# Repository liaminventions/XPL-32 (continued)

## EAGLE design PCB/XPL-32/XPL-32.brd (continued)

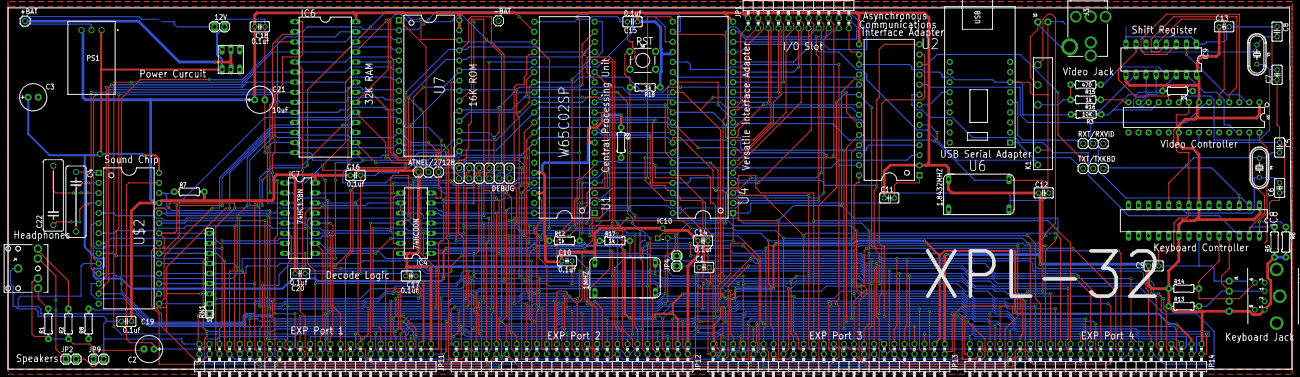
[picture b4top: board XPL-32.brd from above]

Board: 2 copper layers, 323.8 x 91.1 mm, 81 parts (1 on the bottom side), 116 nets.

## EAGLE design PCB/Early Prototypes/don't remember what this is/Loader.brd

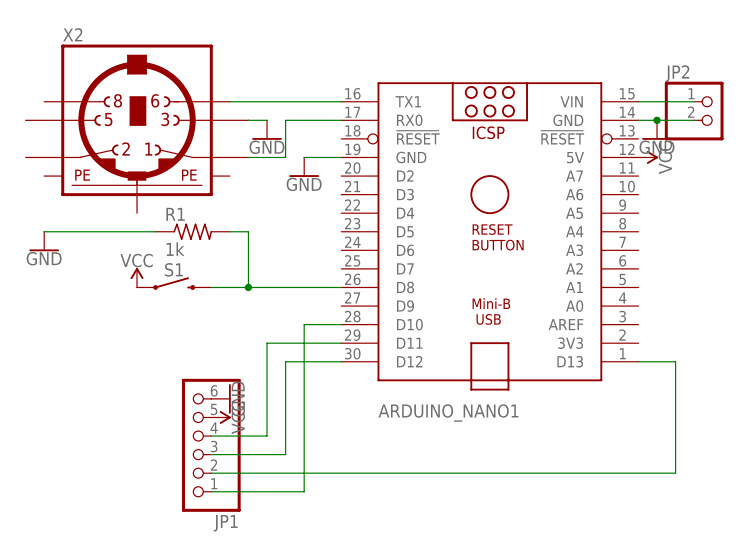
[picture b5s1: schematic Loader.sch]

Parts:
ARDUINO_NANO1: ARDUINO_NANO
JP1: PINHD-1X6; 1X06
JP2: PINHD-1X2; 1X02
R1: 1k; 0204/7
S1: MOMENTARY-SWITCH-SPST-PTH-6.0MM; TACTILE_SWITCH_PTH_6.0MM
X2: MINI_DIN_6; M_DIN6

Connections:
GND: ARDUINO_NANO1.14 (GND), ARDUINO_NANO1.19 (GND), JP1.6, JP2.2, R1.1, X2.3
unnamed: ARDUINO_NANO1.16 (TX1), X2.6
unnamed: ARDUINO_NANO1.17 (RX0), X2.1
unnamed: ARDUINO_NANO1.15 (VIN), JP2.1
unnamed: ARDUINO_NANO1.29 (D11), JP1.4
unnamed: ARDUINO_NANO1.30 (D12), JP1.3
unnamed: ARDUINO_NANO1.1 (D13), JP1.2
unnamed: ARDUINO_NANO1.28 (D10), JP1.1
unnamed: ARDUINO_NANO1.26 (D8), R1.2, S1.3 (2)
PE1: X2.SH1 (PE1)
PE2: X2.SH2 (PE2)
PE3: X2.SH3 (PE3)
VCC: ARDUINO_NANO1.12 (5V), JP1.5, S1.1

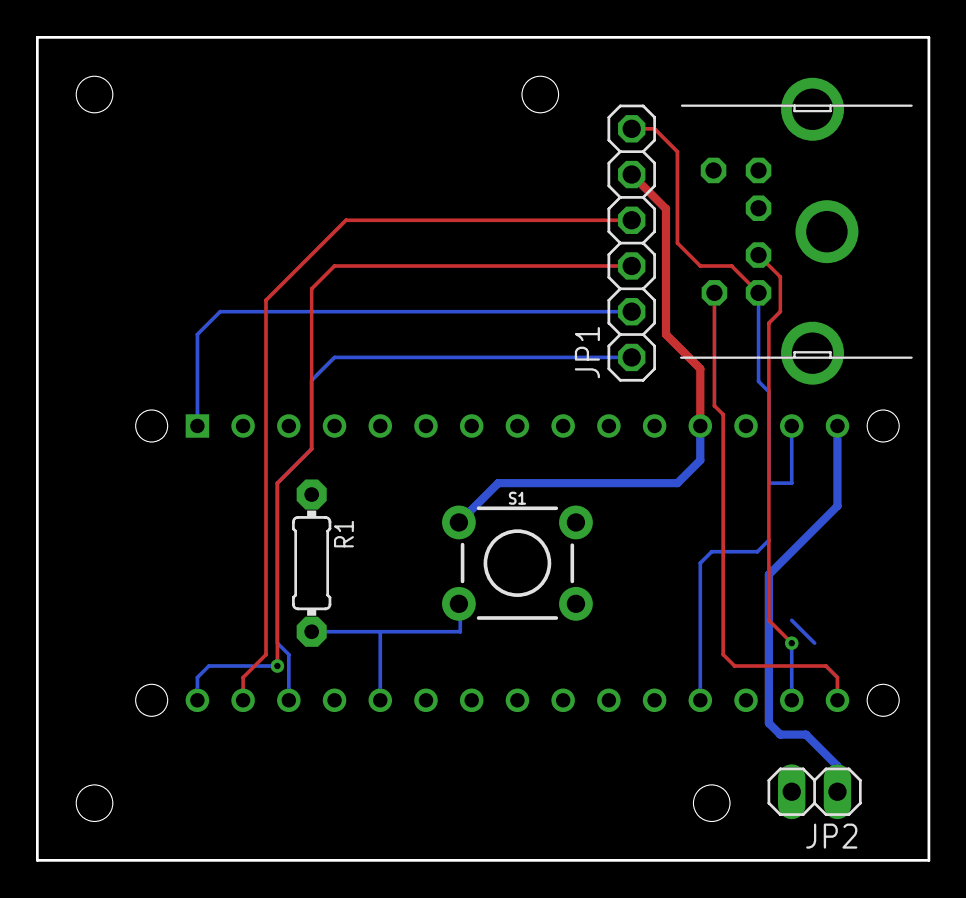
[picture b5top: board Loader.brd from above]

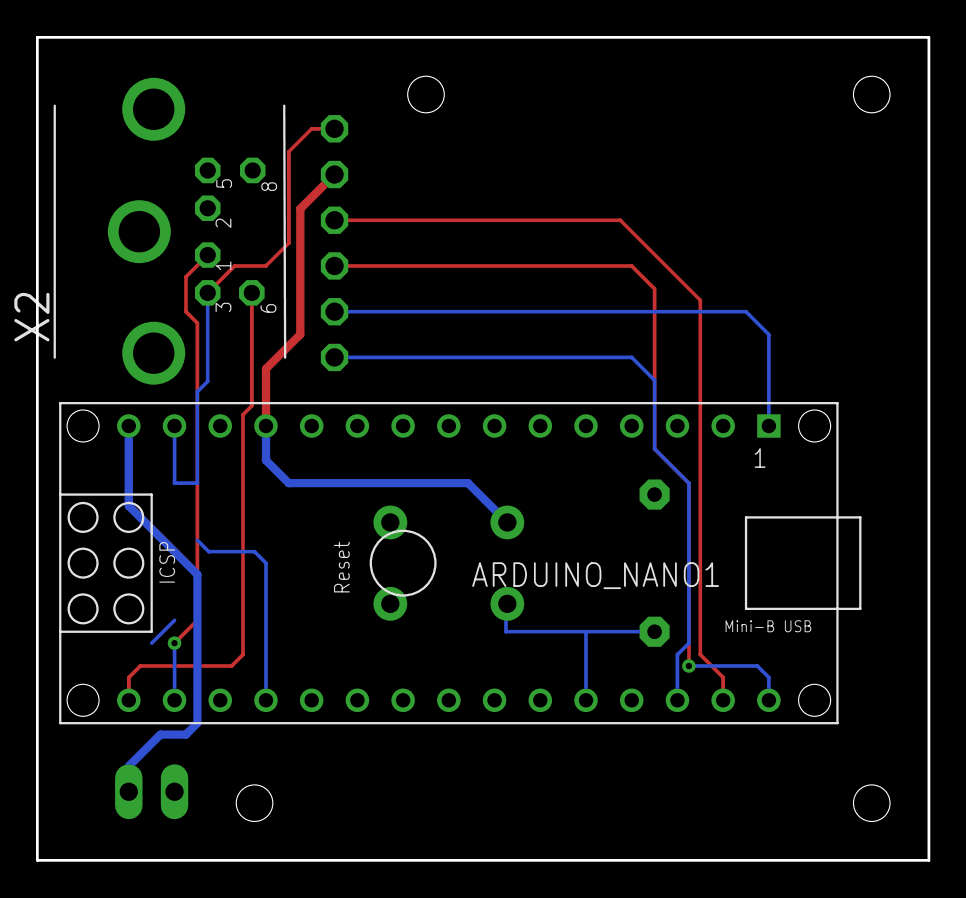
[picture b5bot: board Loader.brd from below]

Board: 2 copper layers, 49.5 x 45.7 mm, 6 parts (2 on the bottom side), 10 nets.

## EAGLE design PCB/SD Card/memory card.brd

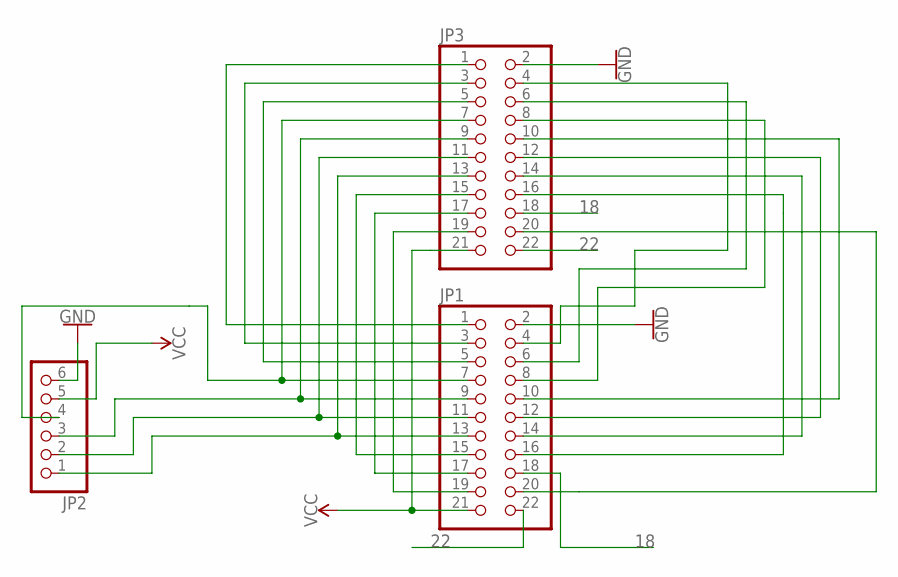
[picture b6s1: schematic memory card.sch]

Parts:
JP1, JP3: PINHD-2X11/90; 2X11/90
JP2: PINHD-1X6; 1X06

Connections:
18: JP1.18, JP3.18
22: JP1.22, JP3.22
GND: JP1.2, JP2.6, JP3.2
unnamed: JP1.20, JP3.20
unnamed: JP1.16, JP3.16
unnamed: JP1.14, JP3.14
unnamed: JP1.8, JP3.8
unnamed: JP1.19, JP3.19
unnamed: JP1.17, JP3.17
unnamed: JP1.15, JP3.15
unnamed: JP1.13, JP2.1, JP3.13
unnamed: JP1.11, JP2.2, JP3.11
unnamed: JP1.9, JP2.3, JP3.9
unnamed: JP1.7, JP2.4, JP3.7
unnamed: JP1.5, JP3.5
unnamed: JP1.3, JP3.3
unnamed: JP1.1, JP3.1
unnamed: JP1.6, JP3.6
unnamed: JP1.4, JP3.4
unnamed: JP1.12, JP3.12
unnamed: JP1.10, JP3.10
VCC: JP1.21, JP2.5, JP3.21

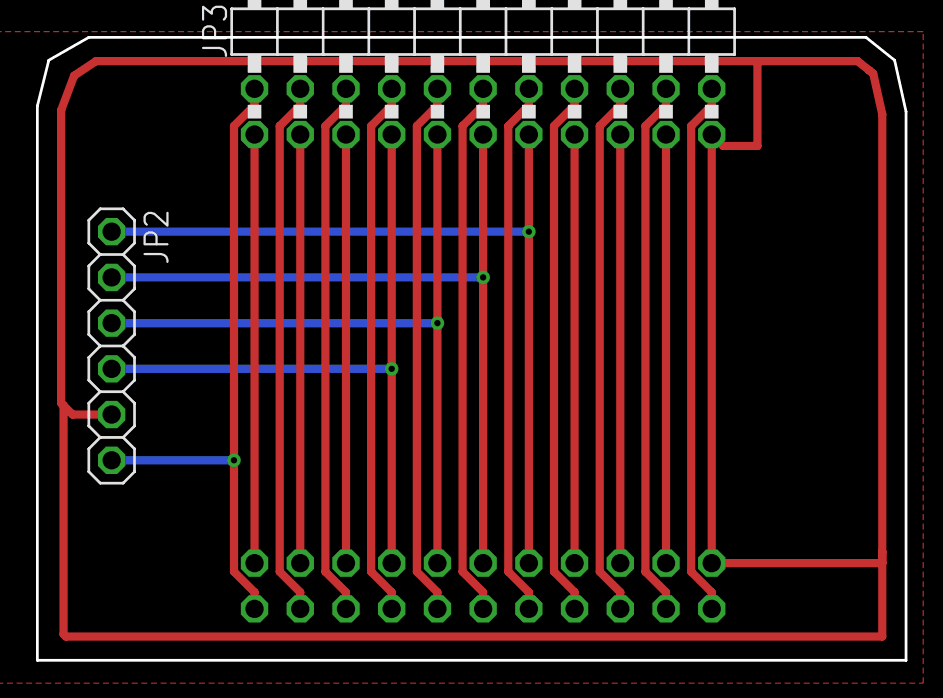
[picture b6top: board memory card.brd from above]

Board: 2 copper layers, 48.3 x 34.6 mm, 3 parts (1 on the bottom side), 22 nets.

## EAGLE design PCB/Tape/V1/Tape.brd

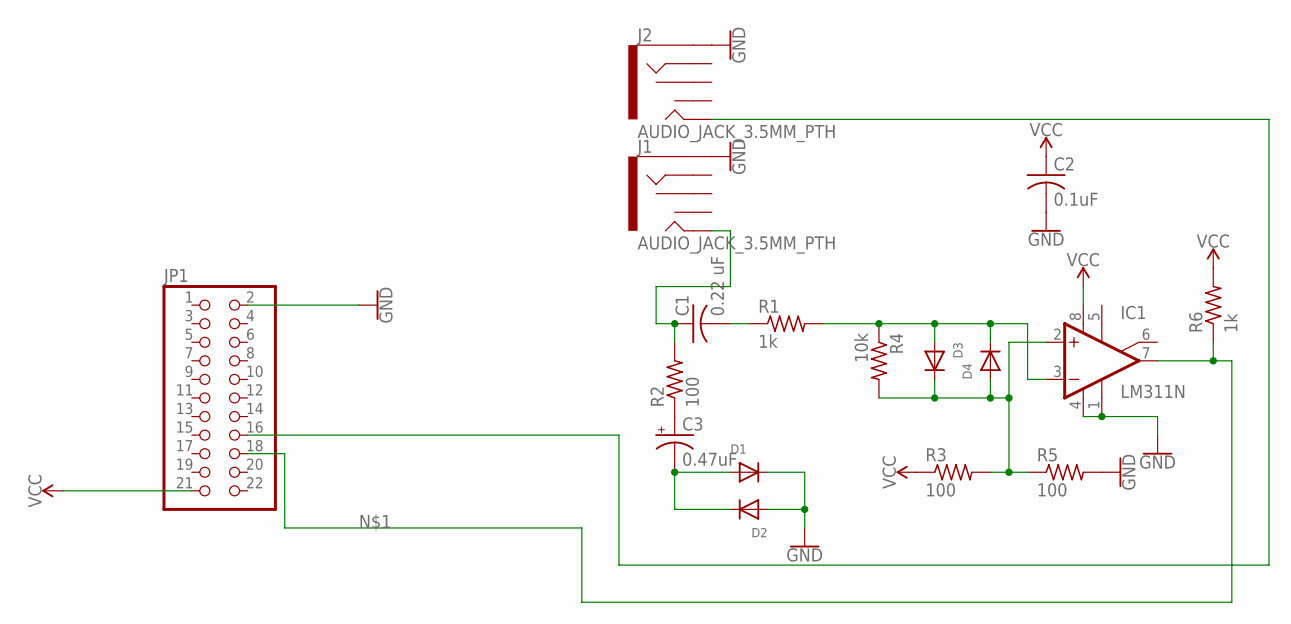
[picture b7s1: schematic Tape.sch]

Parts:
C1: 0.22 uF; C025-030X050
C2: 0.1uF; C025-030X050
C3: 0.47uF; E2,5-5
D1, D2, D3, D4: DIODEDO-1N4148; DO-1N4148
IC1: LM311N; DIL08
J1, J2: AUDIO_JACK_3.5MM_PTH; AUDIO-JACK
JP1: PINHD-2X11/90; 2X11/90
R1, R6: 1k; 0204/7
R2, R3, R5: 100; 0204/7
R4: 10k; 0204/7

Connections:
18: J2.TIP, JP1.16
GND: C2.2, D1.C, D2.A, IC1.1 (GND), IC1.4 (V-), J1.SLEEVE, J2.SLEEVE, JP1.2, R5.2
unnamed: IC1.7 (OUT), JP1.18, R6.1
unnamed: C1.2, R1.1
unnamed: C3.-, D1.A, D2.C
unnamed: C3.+, R2.1
unnamed: D3.A, D4.C, IC1.3 (-IN), R1.2, R4.1
unnamed: D3.C, D4.A, IC1.2 (+IN), R3.2, R4.2, R5.1
unnamed: C1.1, J1.TIP, R2.2
VCC: C2.1, IC1.8 (V+), JP1.21, R3.1, R6.2

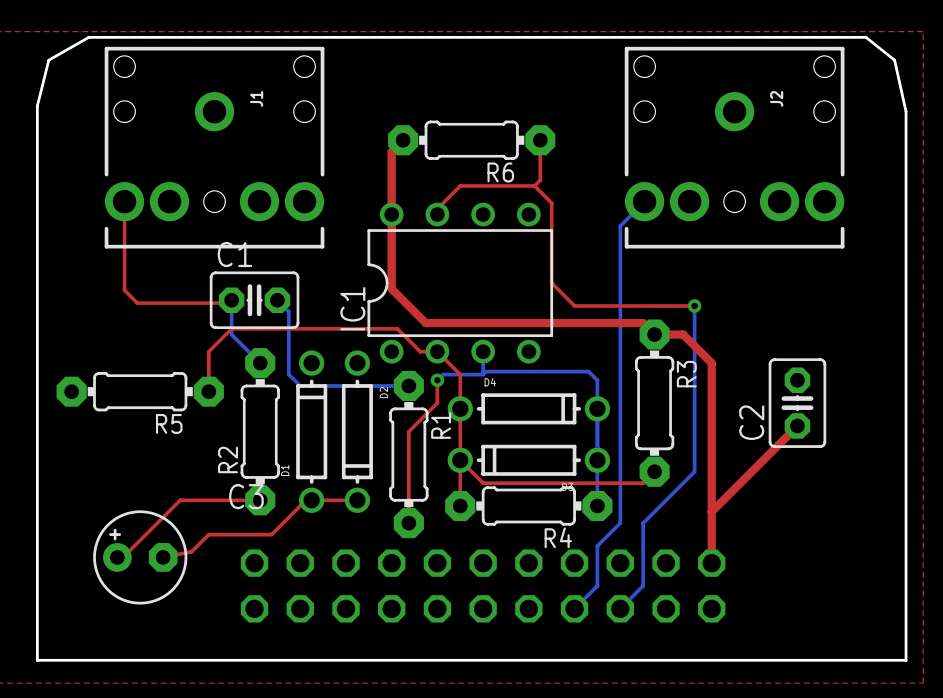
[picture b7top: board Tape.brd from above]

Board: 2 copper layers, 48.3 x 34.6 mm, 17 parts (1 on the bottom side), 10 nets.

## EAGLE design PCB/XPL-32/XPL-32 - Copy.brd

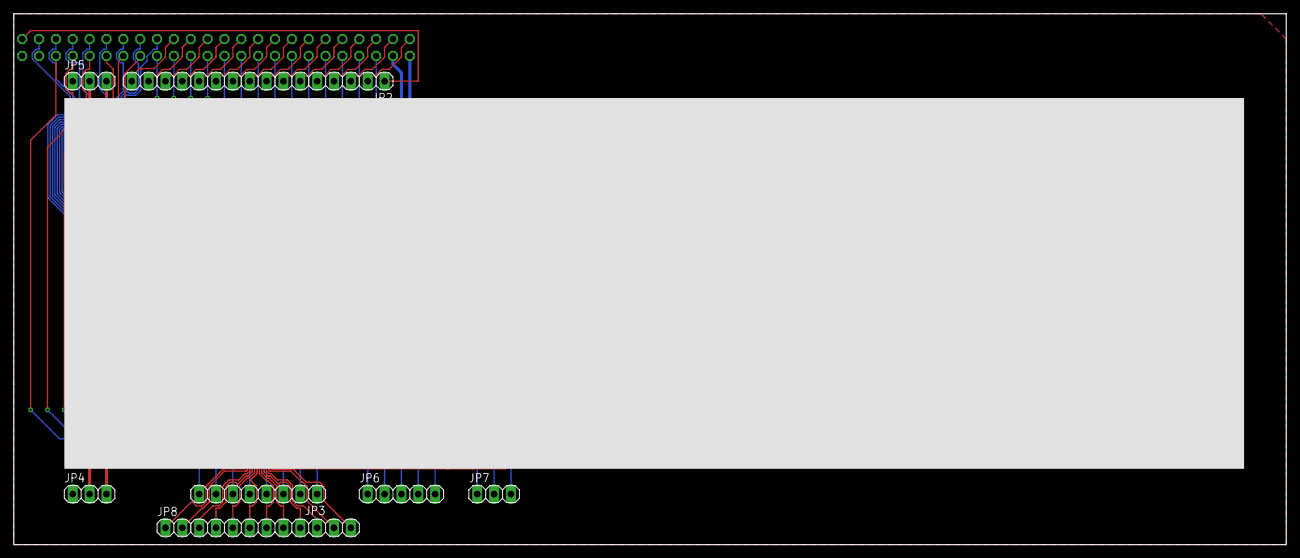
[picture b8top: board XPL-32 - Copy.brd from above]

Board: 2 copper layers, 191.8 x 80.0 mm, 8 parts (1 on the bottom side), 47 nets.

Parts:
JP1: 2X24/90
JP2: 1X16
JP3: 1X08
JP4, JP5, JP7: 1X03
JP6: 1X05
JP8: 1X12

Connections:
!8800-8FFF: JP1.15, JP6.5
!9000-97FF: JP1.17, JP6.4
!9800-9FFF: JP1.19, JP6.3
!A000-A7FF: JP1.21, JP6.2
!A800-AFFF: JP1.23, JP6.1
!CSROM: JP1.7, JP8.11
!IRQ: JP1.25, JP8.7
!OEROM: JP1.5, JP8.12
!READ: JP1.11, JP8.9
!ROM: JP1.9, JP8.10
!RST: JP1.39, JP7.3
!WRITE: JP1.13, JP8.8
A0: JP1.48, JP2.1
A1: JP1.2, JP2.2
A2: JP1.4, JP2.3
A3: JP1.6, JP2.4
A4: JP1.8, JP2.5
A5: JP1.10, JP2.6
A6: JP1.12, JP2.7
A7: JP1.14, JP2.8
A8: JP1.16, JP2.9
A9: JP1.18, JP2.10
A10: JP1.20, JP2.11
A11: JP1.22, JP2.12
A12: JP1.24, JP2.13
A13: JP1.26, JP2.14
A14: JP1.28, JP2.15
A15: JP1.30, JP2.16
AUDIO: JP1.31, JP8.4
CLK: JP1.43, JP7.1
D0: JP1.32, JP3.1
D1: JP1.34, JP3.2
D2: JP1.36, JP3.3
D3: JP1.38, JP3.4
D4: JP1.40, JP3.5
D5: JP1.42, JP3.6
D6: JP1.44, JP3.7
D7: JP1.46, JP3.8
EXTSND: JP1.33, JP8.3
EXTVID: JP1.35, JP8.2
GND: JP1.45, JP1.47, JP4.1, JP5.1
POTX: JP1.29, JP8.5
POTY: JP1.27, JP8.6
R/!W: JP1.41, JP7.2
SCLK: JP1.37, JP8.1
VCC: JP1.1, JP4.2, JP5.2
VCC_2: JP1.3, JP4.3, JP5.3

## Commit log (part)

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2023-01-01 have i fixed shortconvert?
2023-01-01 refactor
2023-01-01 maybe its not this?
2023-01-01 oqwe
2023-01-01 With this debug info, i see the issue
2023-01-01 Complete Refactor of the shortconvert system.
2023-01-01 You will work now.
2023-01-01 oh there it is! hehe
2023-01-01 all done!
2023-01-12 clean
2023-01-12 erjieqw
2023-01-12 i dont have time for this
2023-01-20 organise
2023-01-21 add clear command
2023-01-21 fix typos
2023-01-21 add slashpaths?
2023-01-21 fix addr
2023-01-21 wase of time AUUGH
2023-01-23 kernal
2023-01-24 add goofy ahh vim thingy
    aUUUGHHHHH
2023-01-24 update vi
2023-01-24 eqhruewh
2023-01-24 assemble
2023-01-24 iuir
2023-01-24 bugfix
2023-01-24 asmbler da
2023-01-24 Yes.
2023-01-27 update kernal + rearrange + fix memory overlap
2023-01-27 assemble it all together
2023-01-27 update ROM
2023-01-27 werwe
2023-01-31 ok! lets see what arrow keys are
2023-01-31 ccursor test
2023-01-31 generic commit - pay no mind
2023-02-05 add fast mode?
2023-02-05 sizing fix
2023-02-05 quik fixx
2023-02-05 add artifacts
2023-02-05 size
2023-02-05 fix tape kernal defs
2023-02-09 swap
2023-02-21 do not assemble savetest rn
    full re-write of saving
2023-02-21 he he he haw...
    this fixes lots of things...
2023-02-21 noice!
    do not use fat32 in vasm6502 yet
2023-02-21 oh yeah. this is great!
    lots of improvement, but its untested for now
2023-02-21 fix..?
2023-02-22 LETS GO !!
    i think it's done!!!!!!!
    now to test
2023-02-22 test prep (soon)
2023-02-22 testing now
2023-02-22 fix?
2023-02-22 hoho, i got u
2023-02-22 never gonna give you up
2023-02-22 Be fixed now.
2023-02-22 You are done.
2023-02-22 Fired.
2023-02-22 auugh
2023-02-22 gonna try again tomorrow
2023-02-22 oh
    dtrsynhrth
2023-02-22 ho ho ho!
    it works, but its only half a block
2023-02-22 perfect. sd_writesector works
2023-02-22 debuggin time
2023-02-23 many things :100:
    fixin gliches/debug and fix dumb mistakez (lol)
2023-02-23 remove bloat :alien:
2023-02-23 re-arrange and fix savetest i think
2023-02-23 Looking good...
    can't test it now because I didn't bring the XPL with me (on a trip)
2023-02-23 add issue
    overlooked...
2023-02-23 fix EOC handling in fat32_writesector
2023-02-23 workflow: check if cc65 works in a container
2023-02-23 cleanup
2023-02-25 almost there !! (debuggin)
    auugh i mixed up fat32_writenextsector with sd_writesector. probally somewhere else too, hold on...
2023-02-25 ze big e
2023-02-25 oh im dum
    write! not read!
2023-02-25 argh
2023-02-25 Got You.
    "sky sunday" by sinny
2023-02-25 test without
2023-02-25 OMG IT WOKS!
2023-02-25 almost done fixing filesizes
2023-02-25 update bug count
2023-02-25 this is it...
2023-02-25 test
2023-02-25 wow is that what it is?
2023-02-25 ITS DONE!
    oh my...
2023-02-25 IT WORKS! lets try dumping the ROM...
2023-02-25 stability fix?
2023-02-25 AUGH
2023-02-25 FIXED!
    it works!!!!!!!!!!!!!!!!!!!!!!!!!!!!!!!!!!!!!!!!1
2023-02-25 YES! (delete bloat)
2023-02-26 add delete file and set ROM to 16k
2023-02-26 fix
    arrgh inefficient write amount...
2023-02-26 oh i was just dum
2023-02-26 fix aaaaa
    AUUGH !!
2023-02-26 ohhhhhhh
    ic...
2023-02-26 and that
2023-02-26 YAY! RM WORKS!
2023-02-26 add new fat32/sd features to the monitor
2023-02-26 fix assemble
2023-02-26 compile
2023-02-26 :100: EPIC CODER MOMENT !!
2023-02-26 add sd save to the dispatch table
2023-02-26 OMG IT WORKED!
    save command in the monitor! oh wow...
2023-02-26 add file overwriting
2023-02-26 rm that for FAT stability...
2023-02-26 ohhhh
2023-02-26 Be Fixed.
2023-02-26 ohyeah, now RM
2023-02-26 here
2023-02-26 YEAH! RM AND SAVE WORKS!
2023-02-26 check
2023-02-26 All done for today... that was amazing!
2023-02-26 add executable reconition
2023-02-26 KERNAL: update part 1
2023-02-27 finalize kernal def
    done
2023-02-27 add mv and also maybe fix rm? also cleanup
    gotta assemble this on my raspberry pi - hold on...
2023-02-27 whoops - also i gotta add the new fat routines
2023-02-27 ok now i can test
2023-02-27 one moment
2023-02-27 ffind out
2023-02-27 ohhhh is that it?
2023-02-27 fix merge issue
2023-02-27 rguyiwq
2023-02-27 wakeuhyufgef
2023-02-27 Work.
2023-02-27 auugh!!
2023-02-27 oh.
    AUUGH THATS ALL IT IS??!
2023-02-27 -
    -
2023-02-27 Get out, Bug. You are ruining my life.
2023-03-05 redo some things
2023-03-05 quick fix
2023-03-05 ho ho ho!
2023-03-05 fix root name
2023-03-05 why does it display the matrix on startup..?
2023-03-05 fix root symbol
2023-03-05 ehgr
2023-03-06 lesgo
2023-03-06 add dmf
2023-03-06 new image
2023-03-16 fix no directory being showed after root symbol
2023-03-17 iaehh
2023-03-17 changes to asm.sh and rename tms_groove
2023-03-17 oh. (reorginise)
2023-03-17 copy wavrud.s to pong.s (DO NOT USE YET!)
2023-03-18 pong.s better
2023-03-18 fix stuf
2023-03-18 update sd
2023-03-18 ho ho...
2023-03-18 fix ball center
2023-03-18 aeiohr
2023-03-18 oh yeah...
2023-03-18 add vertical dotted line?
2023-03-18 werhnio
2023-03-19 will this fix the paddles?
2023-03-19 waaa
2023-03-19 weiuoo
2023-03-26 clean up
2023-03-27 begin fat32 experiment
2023-03-27 so the journey begins...
2023-03-27 dont run yet
2023-03-27 remove that darn buffer
2023-03-27 rename sectorbounds as updatefat
2023-03-27 begin cluster logic
2023-03-27 augugt
2023-03-27 the big update
2023-03-27 add eoc
2023-03-27 ok! its testing time!
2023-03-28 grr...
2023-03-28 well! atleast thats a step in the right direction!
    more tomorrow...
2023-03-28 hahaha
2023-03-28 when the rts broke the cpu
2023-03-28 will that solve it?
2023-03-28 dumb
2023-03-28 I DID IT!
2023-03-28 good
2023-03-28 IT WORKS!!
    - 512 bytes!
    + fat mirroring!
2023-03-28 add save example
2023-03-28 remove libfat32-stable, as it is no longer stable...
2023-03-28 hoho
2023-03-29 that seemed broken, but i guess it's okay??
2023-03-31 darn
2023-03-31 ..................oh.
2023-04-01 ohh...
2023-04-01 wkhtw
2023-04-01 hehe
2023-04-02 poiuytrew
2023-04-02 oh...
2023-04-02 v bgfvbgtfvrfv
2023-04-02 certified awesome moment (fixed)
2023-04-02 mv is broken - will fix later
2023-04-02 test2
2023-04-02 all fixed!
2023-04-05 tried out decoding a tape file from the XPL!
    it worked!
2023-04-07 add idea
2023-04-09 stuf
2023-04-11 Pong! (big progress)
2023-04-11 grr..
2023-04-11 hotfix
2023-04-11 er...
2023-04-11 hahahhah
2023-04-11 Will it work now?
2023-04-12 test a
2023-04-14 nvim test
2023-04-14 going to add a new licence
2023-04-24 funny fix..?
2023-04-24 the hek was that
2023-04-24 haha yez
2023-05-07 whoops! that was the wrong xa
2023-05-07 fix 2
2023-05-07 ._.
    shoutout to richard stallman-
2023-05-07 the funi
2023-05-13 add modified sdcard_spi sigrok decoder
2023-05-14 oh dang it
2023-05-14 this is where the VSR is irl
2023-05-19 guh?
2023-06-24 clean part 1
2023-06-24 fix gitignore
2023-06-24 fix2
2023-07-06 whoops
2023-07-08 add sd card glitch (idk yet)
2023-07-10 debugging...
2023-07-10 yes, fixed!
2023-07-11 fix shortconvert
2023-07-11 huh?
2023-07-11 is that it?
2023-07-11 ah ok.
2023-07-11 add line ending detection to CAT
2023-07-11 lol i forgot
2023-07-12 huh ok
2023-07-12 why did i do that
2024-10-05 new pcb!!
    this will make it possible to work on the sd card thing yet again!!
2025-06-27 me and xat - WE DID IT.
    sd saving fixed
    i think.
2025-06-27 lemme just put that back lol
2025-06-28 part
2025-06-28 cd fixed, now to restore all other cmds
2025-06-28 change it back!!
    (for now)
2025-06-29 fix error handling
    lol
2025-06-29 ls now uses new path sys
2025-06-30 a bit more fixed ig
